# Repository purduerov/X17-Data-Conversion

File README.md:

# X17-Data-Conversion
This board converts PMBus to RS485

Whenever you make a new part, download the datasheet and save it here _**and**_ with the part in the parts library

Always pull other people's changes before beginning to work
`git pull`

Be sure to push your changes after  working on them. Run:
1. `git add .` to add any files in this directory or a subdirectory
or `git add -u` to add any modified files
2. (Optional) `git clean -nX` to see what ignored files can be removed
	`git clean -fX` removes ignored files (Eagle backups)
3. `git commit -m "helpful commit message"` with a description of the work that you did
4. `git push` to push your work to github

Other helpful commands
* `git status` says information about modified and staged files
* `git log` shows the recent commits of the repository
* `git log filename.extension` show the recent commits for just that file
* `git checkout first-couple-letter-of-commit-id` lets you go back to a previous version
* `git checkout master` brings you back to the latest commit
* `git tag` lists the tags
* `git tag -a orderX -m "the version of the board placed for the X'th order"` tag a specific commit
* `git push --tags` needed to push tags to remote
* `git show orderX` show the commit log for the given tag
* `git checkout orderX` go back and interact with the files at the tagged commit

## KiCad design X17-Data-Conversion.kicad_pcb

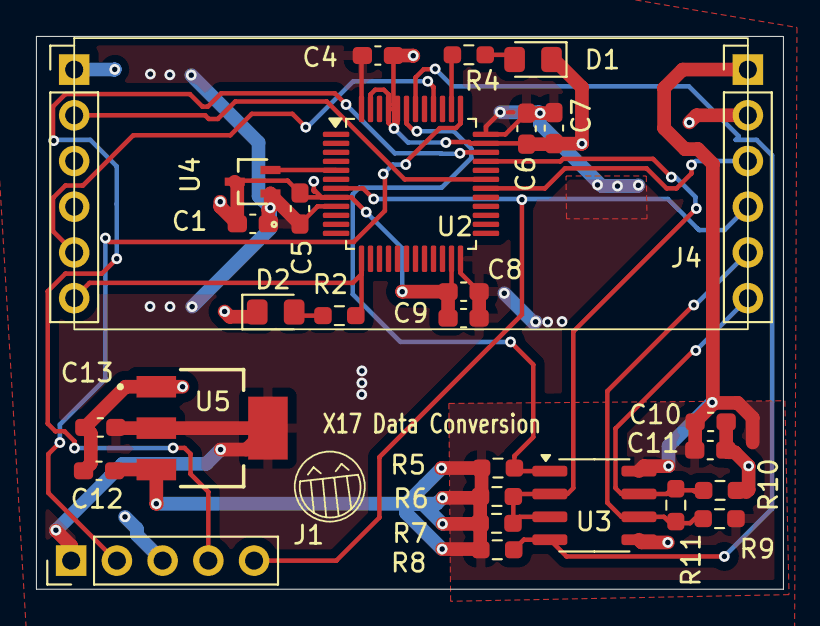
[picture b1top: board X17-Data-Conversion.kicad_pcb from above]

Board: 2 copper layers, 41.5 x 30.7 mm, 28 parts (0 on the bottom side), 19 nets.

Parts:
C1, C4, C5, C6, C9: 0.1uF; C_0603_1608Metric_Pad1.08x0.95mm_HandSolder
C7, C8: 4.7uF; C_0603_1608Metric_Pad1.08x0.95mm_HandSolder
C10, C12: 10uF; C_0603_1608Metric_Pad1.08x0.95mm_HandSolder
C11: .1uF; C_0603_1608Metric_Pad1.08x0.95mm_HandSolder
C13: 22uF; C_0603_1608Metric_Pad1.08x0.95mm_HandSolder
D1, D2: LED; LED_0805_2012Metric_Pad1.15x1.40mm_HandSolder
J1: Conn_01x05; PinHeader_1x05_P2.54mm_Vertical
J4: Conn_01x12_Pin; Data Conversion two 1x6
R2, R4: 470; R_0603_1608Metric_Pad0.98x0.95mm_HandSolder
R5, R6, R7, R8: 10000; R_0603_1608Metric_Pad0.98x0.95mm_HandSolder
R9, R10: 20000; R_0603_1608Metric_Pad0.98x0.95mm_HandSolder
R11: 120; R_0603_1608Metric_Pad0.98x0.95mm_HandSolder
U2: STM32F091CCTx; LQFP-48_7x7mm_P0.5mm
U3: MAX485E; SOIC-8_3.9x4.9mm_P1.27mm
U4: MAX7375AXR805+T; 21-0075D_MXM
U5: AZ1117IH-3.3TRG1; SOT230P700X185-4N

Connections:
3.3V: C1.1, C4.2, C5.2, C6.2, C7.2, C8.2, C9.2, C13.1, J1.1, U2.9 (VDDA), U2.24 (VDD), U2.36 (VDDIO2), U2.48 (VDD), U4.1 (V+), U5.2 (OUTPUT), U5.4 (VOUT)
5V: C10.1, C11.1, C12.2, J4.7, R5.1, R6.1, R7.1, R8.1, R9.1, U3.8 (VCC), U5.3 (INPUT)
A+: J4.11, R9.2, R11.2, U3.6 (A)
A-: J4.12, R10.1, R11.1, U3.7 (B)
ALERT1: J4.5, U2.40 (PB4)
GND: C1.2, C4.1, C5.1, C6.1, C7.1, C8.1, C9.1, C10.2, C11.2, C12.1, C13.2, D1.1 (K), D2.1 (K), J1.3, J4.1, J4.8, R10.2, U2.8 (VSSA), U2.23 (VSS), U2.35 (VSS), U2.44 (PF11), U2.45 (PB8), U2.47 (VSS), U3.5 (GND), U4.3 (GND), U5.1 (GND)
I2C1_SCL: J4.9, U2.30 (PA9)
I2C1_SDA: J4.2, U2.31 (PA10)
NRST_PSB: J1.5, J4.10, U2.7 (NRST)
unnamed: D1.2 (A), R4.2
unnamed: D2.2 (A), R2.2
unnamed: R4.1, U2.38 (PA15)
unnamed: U2.5 (PF0), U4.2 (CLOCK)
PG: J4.6, R2.1, U2.13 (PA3)
SWCLK: J1.2, U2.37 (PA14)
SWDIO: J1.4, U2.34 (PA13)
USART1_DE: R6.2, R7.2, U2.33 (PA12), U3.2 (~RE), U3.3 (DE)
USART1_RX: R5.2, U2.43 (PB7), U3.1 (RO)
USART1_TX: R8.2, U2.42 (PB6), U3.4 (DI)

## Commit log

2024-12-18 creating files
2024-12-18 My STM32 stuff
    Includes STM32 sheet, RS485 sheet, and a power flags list (not all will be used)
2024-12-19 Leo's Winter break first fixes
    Updates fixing the capacitor for the switch
2024-12-19 Edits part two
    Deleted CAN as not needed in X17
2024-12-19 Binary file has changed?
    not too sure but gonna commit.
2024-12-19 Edits part 3
    Added the two new 1 by 6 vertical pin connectors to the schematic, the layout is a bit buggy tho, need to work on that next.
2024-12-20 Edit 4
    Moved on to the layout process, then had trouble with the new connectors J2 J3 as they did not show up.
2024-12-22 All Layout points are fixed
    the layout now has all the components without errors or warnings. However, GND and NRST are all connected.
2024-12-22 Updates
    Now the GND and NRST are not fully interconnected and overlapping each others signals.
2024-12-22 Layout is somewhat laid out.
2024-12-27 3.3V and GND is whats left
    All my changes are included. All layout is finished except for 3.3V and GND
2024-12-27 included name
2024-12-28 if this goes wrong mb
2024-12-28 DRC process
    3 errors
    4 warnings
2024-12-29 Should be finished.
2024-12-30 Redid to meet specifications no drcs
2024-12-30 extra stuff
2024-12-30 meeting today, need to rewire
2024-12-30 prep to start final (hopefully) layout
2025-01-01 hny!
    lookinggood, happy new year!
2025-01-02 lqwkrjfsadklj
2025-01-02 goodie
    going good
2025-01-02 finished!!!! RAHHHH
    RAHHHHHHHHHHH
2025-01-03 Create ~X17-Data-Conversion.kicad_pcb.lck
    push
2025-01-03 errors
    no errors
2025-01-03 Update X17-Data-Conversion.kicad_pcb
    uipdate
2025-01-03 daniel lookie
2025-01-03 done for now
2025-01-03 here ya go
    here ya go
2025-01-06 BOM first review finished
2025-01-10 1/10/25 gerber files
